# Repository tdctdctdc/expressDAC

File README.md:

# expressDAC

PCB ordered

Proof of concept for a ExpressCard DAC

Using a TI part (PCM2704C) that does all the hard work (USB bridge + DAC) just to prove feasibility. It should be USB Audio class and need no driver whatsoever

Had to change the amplifier chip twice because of the shortage and it's pretty much the least interesting part. The LM4917 is very underwhelming compared to recent TI integrated, 3V3 headphone amplifier

The PCM2704C datasheet is very short (less than 50 pages for 4 variants of the chip !) and power supply rules are not clear. That's why there so many solder bridge. 

Also had to go with awkward footprints for the LDO and EEPROM because it's 2021 and everything is out of stock...

The main goal is to go noise free even with sensitive IEM.

Will be using salvaged expressCard connector since the only available commercial reference (100305702112lf) is on Arrow and I can't order it here.

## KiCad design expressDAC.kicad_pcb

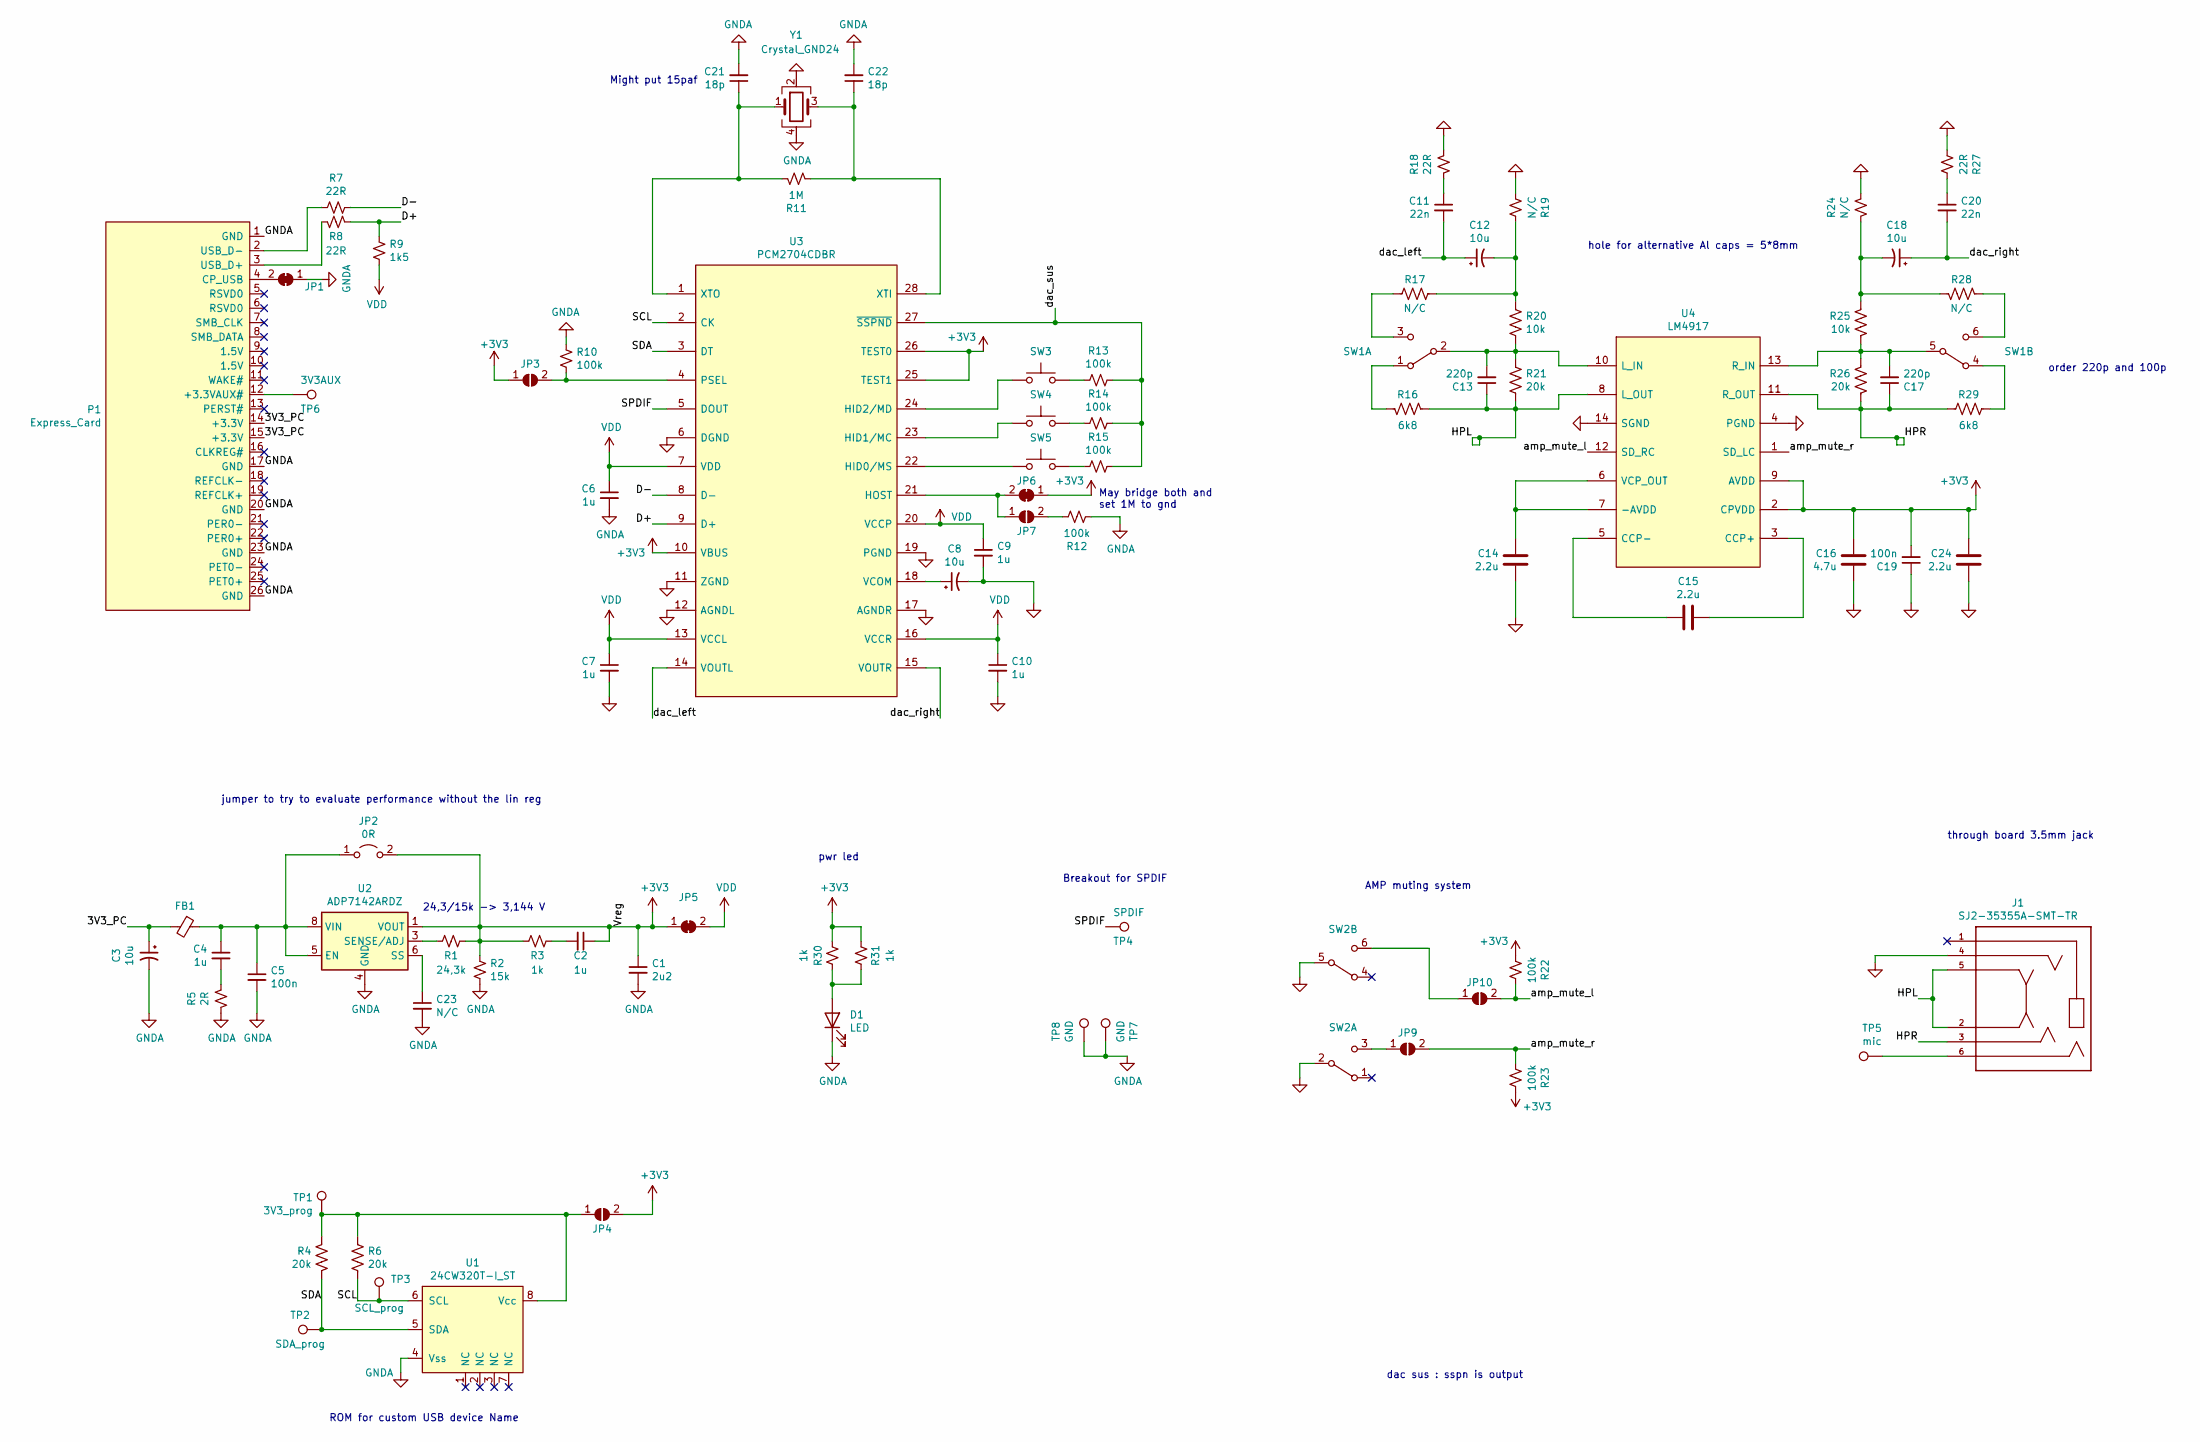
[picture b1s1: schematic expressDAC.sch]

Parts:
C1: 2u2; C_0805_2012Metric_Pad1.18x1.45mm_HandSolder
C2, C4, C6, C7, C9, C10: 1u; C_0805_2012Metric_Pad1.18x1.45mm_HandSolder
C3, C8: 10u; C_0805_2012Metric_Pad1.18x1.45mm_HandSolder
C5, C19: 100n; C_0805_2012Metric_Pad1.18x1.45mm_HandSolder
C11, C20: 22n; C_0805_2012Metric_Pad1.18x1.45mm_HandSolder
C12, C18: 10u; CP_EIA-3528-21_Kemet-B_Pad1.50x2.35mm_HandSolder
C13, C17: 220p; C_0805_2012Metric_Pad1.18x1.45mm_HandSolder
C14, C15, C24: 2.2u; C_0805_2012Metric_Pad1.18x1.45mm_HandSolder
C16: 4.7u; C_0805_2012Metric_Pad1.18x1.45mm_HandSolder
C21, C22: 18p; C_0603_1608Metric_Pad1.08x0.95mm_HandSolder
C23: N/C; C_0805_2012Metric_Pad1.18x1.45mm_HandSolder
D1: LED; D_0805_2012Metric
FB1: Ferrite_Bead_Small; C_1206_3216Metric_Pad1.33x1.80mm_HandSolder
J1: SJ2-35355A-SMT-TR; CUI_SJ2-35355A-SMT-TR; MPN SJ2-35355A-SMT-TR
JP1, JP5, JP6: SolderJumper_2_Bridged; SolderJumper-2_P1.3mm_Bridged_RoundedPad1.0x1.5mm
JP2: 0R; R_0805_2012Metric_Pad1.20x1.40mm_HandSolder
JP3, JP4, JP7, JP9, JP10: SolderJumper_2_Open; SolderJumper-2_P1.3mm_Open_RoundedPad1.0x1.5mm
P1: Express_Card; generic_expresscard
R1: 24,3k; R_0805_2012Metric_Pad1.20x1.40mm_HandSolder
R2: 15k; R_0805_2012Metric_Pad1.20x1.40mm_HandSolder
R3, R30, R31: 1k; R_0805_2012Metric_Pad1.20x1.40mm_HandSolder
R4, R6, R21, R26: 20k; R_0805_2012Metric_Pad1.20x1.40mm_HandSolder
R5: 2R; R_0805_2012Metric_Pad1.20x1.40mm_HandSolder
R7, R8, R18, R27: 22R; R_0805_2012Metric_Pad1.20x1.40mm_HandSolder
R9: 1k5; R_0805_2012Metric_Pad1.20x1.40mm_HandSolder
R10, R12, R13, R14, R15, R22, R23: 100k; R_0805_2012Metric_Pad1.20x1.40mm_HandSolder
R11: 1M; R_0805_2012Metric_Pad1.20x1.40mm_HandSolder
R16, R29: 6k8; R_0805_2012Metric_Pad1.20x1.40mm_HandSolder
R17, R19, R24, R28: N/C; R_0805_2012Metric_Pad1.20x1.40mm_HandSolder
R20, R25: 10k; R_0805_2012Metric_Pad1.20x1.40mm_HandSolder
SW1, SW2: SW_DPDT_x2; AYZ0202AGRLC
SW3, SW4, SW5: SW_DPDT_x2; PTS526SM08SMTR2LFS
TP1: 3V3_prog; TestPoint_Pad_D2.5mm
TP2: SDA_prog; TestPoint_Pad_D2.5mm
TP3: SCL_prog; TestPoint_Pad_D2.5mm
TP4: SPDIF; TestPoint_Pad_D3.0mm
TP5: mic; TestPoint_Pad_D3.0mm
TP6: 3V3AUX; TestPoint_Pad_D3.0mm
TP7, TP8: GND; TestPoint_Pad_D3.0mm
U1: 24CW320T-I_ST; TSSOP-8_4.4x3mm_P0.65mm
U2: ADP7142ARDZ; SOIC-8-1EP_3.9x4.9mm_P1.27mm_EP2.29x3mm
U3: PCM2704CDBR; SOP65P780X200-28N; Mouser Part Number 595-PCM2704CDBR
U4: LM4917; SOP65P640X120-14N; Mouser Part Number 926-LM4917MTX/NOPB
Y1: Crystal_GND24; Crystal_SMD_Abracon_ABM3C-4Pin_5.0x3.2mm

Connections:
+3V3: C1.1, C2.1, C16.2, C19.2, C24.2, JP2.2 (B), JP3.1 (A), JP4.2 (B), JP5.1 (A), JP6.1 (A), R1.2, R2.1, R3.1, R22.2, R23.1, R30.1, R31.2, U2.1 (VOUT), U2.2 (VOUT), U3.10 (VBUS), U3.25 (TEST1), U3.26 (TEST0), U4.2 (CPVDD), U4.9 (AVDD)
/3V3_PC: C3.1, FB1.2, P1.14 (+3.3V), P1.15 (+3.3V)
/D+: R8.1, R9.1, U3.9 (D+)
/D-: R7.1, U3.8 (D-)
/HPL: C13.1, J1.2, J1.5, R16.1, R21.2, U4.8 (L_OUT)
/HPR: C17.1, J1.3, R26.2, R29.1, U4.11 (R_OUT)
/SCL: R6.2, TP3.1, U1.6 (SCL), U3.2 (CK)
/SDA: R4.2, TP2.1, U1.5 (SDA), U3.3 (DT)
/SPDIF: TP4.1, U3.5 (DOUT)
/amp_mute_l: JP10.2 (B), R22.1, U4.12 (SD_RC)
/amp_mute_r: JP9.2 (B), R23.2, U4.1 (SD_LC)
/dac_left: C11.2, C12.1, U3.14 (VOUTL)
/dac_right: C18.1, C20.2, U3.15 (VOUTR)
/dac_sus: R13.1, R14.1, R15.1, U3.27 (~SSPND)
GNDA: C1.2, C3.2, C5.2, C6.2, C7.2, C8.2, C9.2, C10.2, C14.1, C16.1, C19.1, C21.2, C22.2, C23.2, C24.1, D1.1 (K), J1.4, JP1.1 (A), P1.1 (GND), P1.17 (GND), P1.20 (GND), P1.23 (GND), P1.26 (GND), R2.2, R5.1, R10.1, R12.2, R18.2, R19.2, R24.2, R27.2, SW2.2 (B), SW2.5 (B), TP7.1, TP8.1, U1.4 (Vss), U2.4 (GND), U2.9 (GND), U3.6 (DGND), U3.11 (ZGND), U3.12 (AGNDL), U3.17 (AGNDR), U3.19 (PGND), U4.4 (PGND), U4.14 (SGND), Y1.2, Y1.4
unnamed: C2.2, R3.2
unnamed: C4.1, C5.1, FB1.1, JP2.1 (A), U2.5 (EN), U2.7 (VIN), U2.8 (VIN)
unnamed: C4.2, R5.2
unnamed: C8.1, U3.18 (VCOM)
unnamed: C11.1, R18.1
unnamed: C12.2, R17.1, R19.1, R20.1
unnamed: C13.2, R20.2, R21.1, SW1.2 (B), U4.10 (L_IN)
unnamed: C14.2, U4.6 (VCP_OUT), U4.7 (-AVDD)
unnamed: C15.1, U4.3 (CCP+)
unnamed: C15.2, U4.5 (CCP-)
unnamed: C17.2, R25.2, R26.1, SW1.5 (B), U4.13 (R_IN)
unnamed: C18.2, R24.1, R25.1, R28.1
unnamed: C20.1, R27.1
unnamed: C21.1, R11.2, U3.1 (XTO), Y1.1
unnamed: C22.1, R11.1, U3.28 (XTI), Y1.3
unnamed: C23.1, U2.6 (SS)
unnamed: D1.2 (A), R30.2, R31.1
unnamed: J1.6, TP5.1
unnamed: JP1.2 (B), P1.4 (CP_USB)
unnamed: JP3.2 (B), R10.2, U3.4 (PSEL)
unnamed: JP4.1 (A), R4.1, R6.1, TP1.1, U1.8 (Vcc)
unnamed: JP6.2 (B), JP7.1 (A), U3.21 (HOST)
unnamed: JP7.2 (B), R12.1
unnamed: JP9.1 (A), SW2.3 (C)
unnamed: JP10.1 (A), SW2.6 (C)
unnamed: P1.2 (USB_D-), R7.2
unnamed: P1.3 (USB_D+), R8.2
unnamed: P1.12 (+3.3VAUX#), TP6.1
unnamed: R1.1, U2.3 (SENSE/ADJ)
unnamed: R13.2, SW3.1
unnamed: R14.2, SW4.1
unnamed: R15.2, SW5.2
unnamed: R16.2, SW1.1 (A)
unnamed: R17.2, SW1.3 (C)
unnamed: R28.2, SW1.6 (C)
unnamed: R29.2, SW1.4 (A)
unnamed: SW3.2, U3.24 (HID2/MD)
unnamed: SW4.2, U3.23 (HID1/MC)
unnamed: SW5.1, U3.22 (HID0/MS)
VDD: C6.1, C7.1, C9.1, C10.1, JP5.2 (B), R9.2, U3.7 (VDD), U3.13 (VCCL), U3.16 (VCCR), U3.20 (VCCP)

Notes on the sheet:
24,3/15k -> 3,144 V
May bridge both and set 1M to gnd
dac sus : sspn is output
order 220p and 100p
Might put 15paf
hole for alternative Al caps = 5*8mm
ROM for custom USB device Name
jumper to try to evaluate performance without the lin reg
AMP muting system
Breakout for SPDIF
pwr led
through board 3.5mm jack

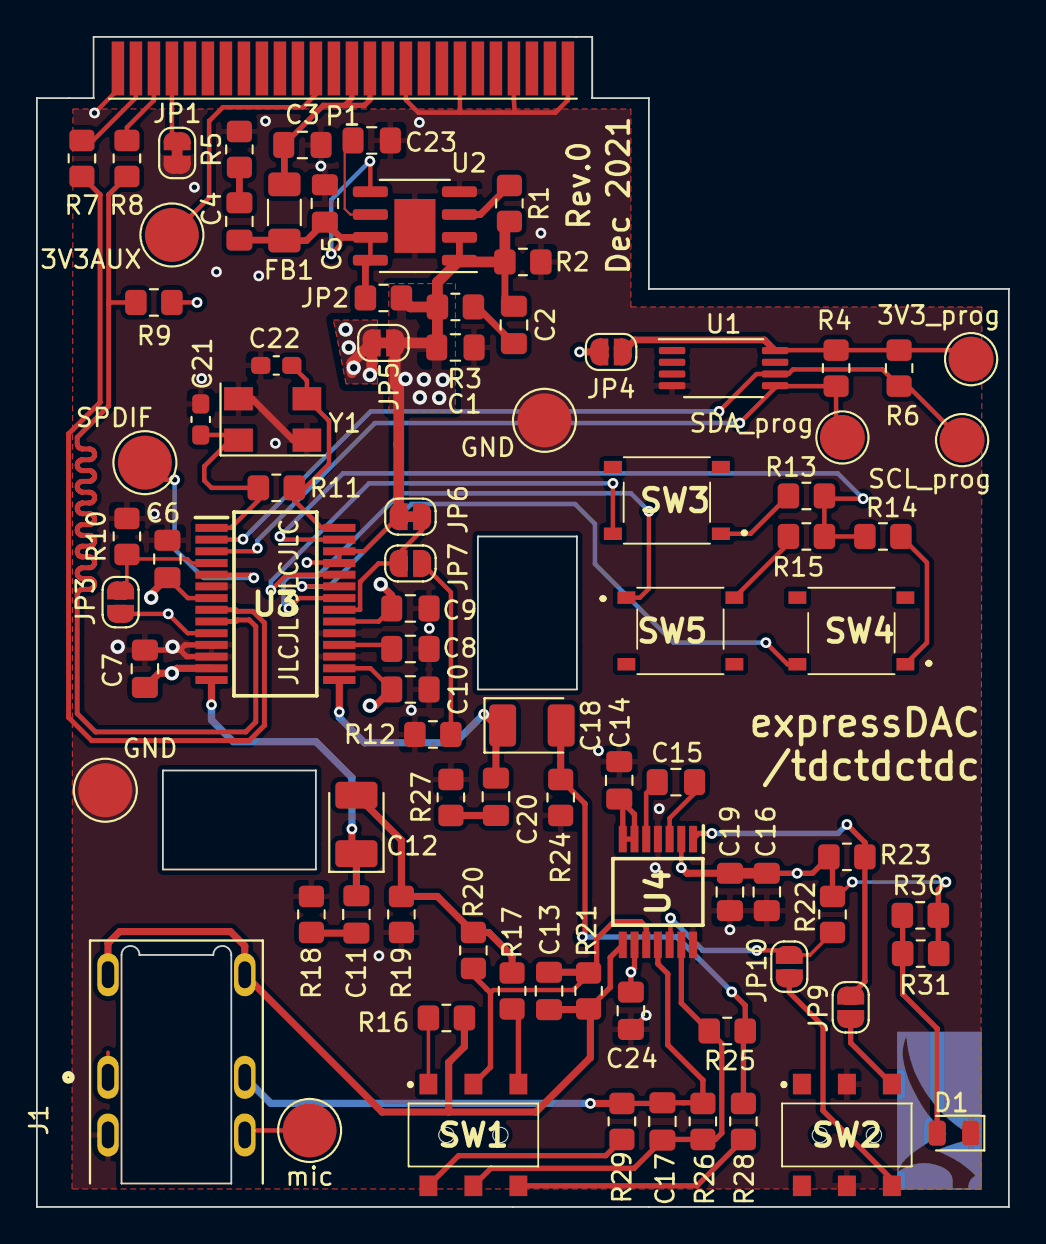
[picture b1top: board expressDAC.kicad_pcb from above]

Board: 4 copper layers, 54.0 x 65.0 mm, 86 parts (0 on the bottom side), 55 nets.

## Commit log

2022-01-01 final version of prototype
